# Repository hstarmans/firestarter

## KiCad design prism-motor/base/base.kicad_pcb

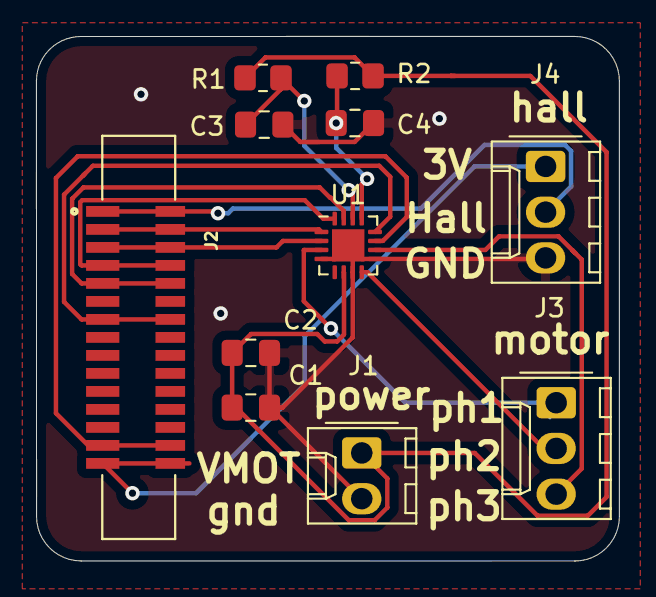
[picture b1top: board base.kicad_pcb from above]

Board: 2 copper layers, 32.4 x 29.1 mm, 11 parts (0 on the bottom side), 15 nets.

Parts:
C1, C3, C4: 10nF; C_0805_2012Metric_Pad1.18x1.45mm_HandSolder
C2: 100nF; C_0805_2012Metric_Pad1.18x1.45mm_HandSolder
J1: Conn_01x02; Molex_KK-254_AE-6410-02A_1x02_P2.54mm_Vertical
J2: 1-1734248-5; TE_1-1734248-5
J3, J4: Conn_01x03; Molex_KK-254_AE-6410-03A_1x03_P2.54mm_Vertical
R1, R2: 10K; R_0805_2012Metric_Pad1.20x1.40mm_HandSolder
U1: STSPIN230; VQFN-16-1EP_3x3mm_P0.5mm_EP1.8x1.8mm

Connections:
+3V3: J2.15, J2.15_1, J4.1
+5V: C1.1, C2.1, J1.1, R1.1, R2.1, U1.6
GND: C1.2, C2.2, C3.2, C4.2, J1.2, J4.3, U1.4, U1.7, U1.9, U1.17
HALL: J2.1, J2.1_1, J4.2
unnamed: C3.1, R1.2, U1.14
unnamed: C4.1, R2.2, U1.13
PH1: J3.1, U1.3
PH2: J3.2, U1.8
PH3: J3.3, U1.10
PWM1H: J2.2, J2.2_1, U1.1
PWM1L: J2.3, J2.3_1, U1.2
PWM2H: J2.4, J2.4_1, U1.16
PWM2L: J2.5, J2.5_1, U1.15
PWM3H: J2.7, J2.7_1, U1.12
PWM3L: J2.14, J2.14_1, U1.11

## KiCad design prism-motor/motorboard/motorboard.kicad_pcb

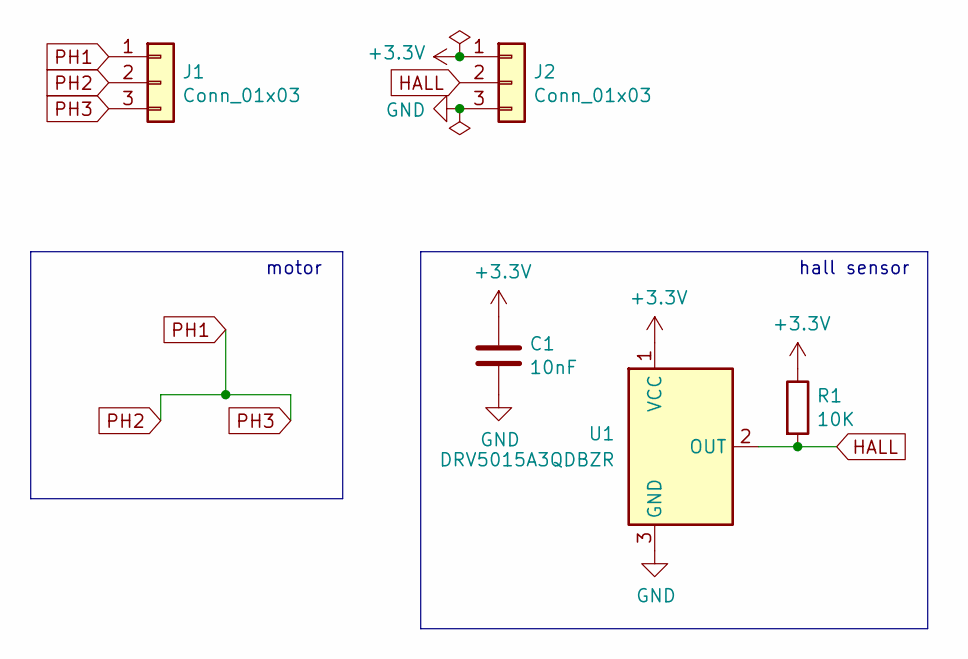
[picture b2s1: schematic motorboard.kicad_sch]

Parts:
C1: 10nF; C_0805_2012Metric_Pad1.18x1.45mm_HandSolder
J1, J2: Conn_01x03; Molex_KK-254_AE-6410-03A_1x03_P2.54mm_Vertical
R1: 10K; R_0805_2012Metric_Pad1.20x1.40mm_HandSolder
U1: DRV5015A3QDBZR; SOT-23

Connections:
+3V3: C1.1, J2.1, R1.1, U1.1 (VCC)
GND: C1.2, J2.3, U1.3 (GND)
HALL: J2.2, R1.2, U1.2 (OUT)
PH1: J1.1, J1.2, J1.3

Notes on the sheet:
motor
hall sensor

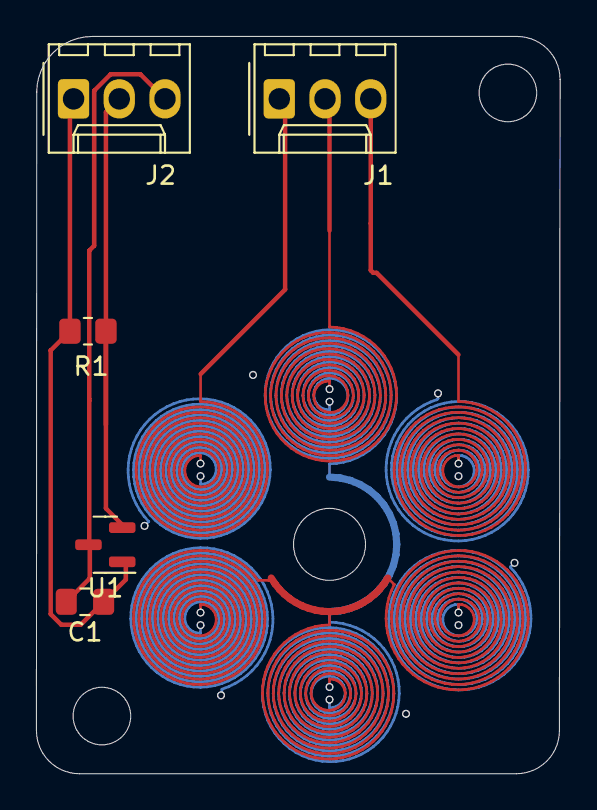
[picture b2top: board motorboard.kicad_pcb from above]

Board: 4 copper layers, 29.1 x 41.0 mm, 5 parts (0 on the bottom side), 4 nets.
